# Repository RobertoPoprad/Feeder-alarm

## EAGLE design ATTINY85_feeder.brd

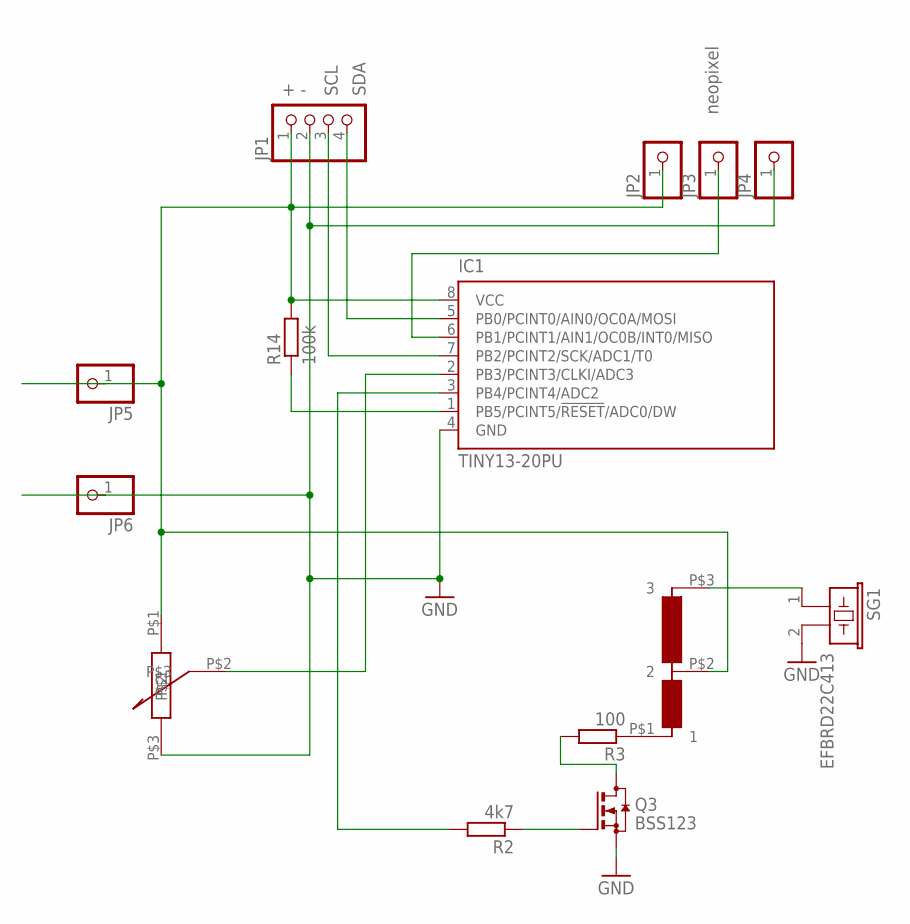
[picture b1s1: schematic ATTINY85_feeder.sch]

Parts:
IC1: TINY13-20PU; DIL08
JP1: PINHD-1X4; 1X04
JP2, JP3, JP4, JP5, JP6: PINHD-1X1; 1X01
Q3: BSS123; SOT23
R2: 4k7; 0204/7
R3: 100; 0204/7
R14: 100k; 0204/7
SG1: EFBRD22C413
U$1: POTENCIOMETER
U$3: AUTOTRAFO

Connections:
GND: IC1.4 (GND), JP1.2, JP4.1, JP6.1, Q3.2 (S), SG1.2, U$1.P$3
unnamed: IC1.3 (PB4/PCINT4/ADC2), R2.2
unnamed: IC1.6 (PB1/PCINT1/AIN1/OC0B/INT0/MISO), JP3.1
unnamed: IC1.7 (PB2/PCINT2/SCK/ADC1/T0), JP1.3
unnamed: IC1.2 (PB3/PCINT3/CLKI/ADC3), U$1.P$2
unnamed: IC1.5 (PB0/PCINT0/AIN0/OC0A/MOSI), JP1.4
unnamed: IC1.1 (PB5/PCINT5/!RESET!/ADC0/DW), R14.1
unnamed: R3.1, U$3.P$1 (1)
unnamed: Q3.1 (G), R2.1
unnamed: SG1.1, U$3.P$3 (3)
unnamed: Q3.3 (D), R3.2
unnamed: IC1.8 (VCC), JP1.1, JP2.1, JP5.1, R14.2, U$1.P$1, U$3.P$2 (2)

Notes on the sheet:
SCL
SDA
neopixel

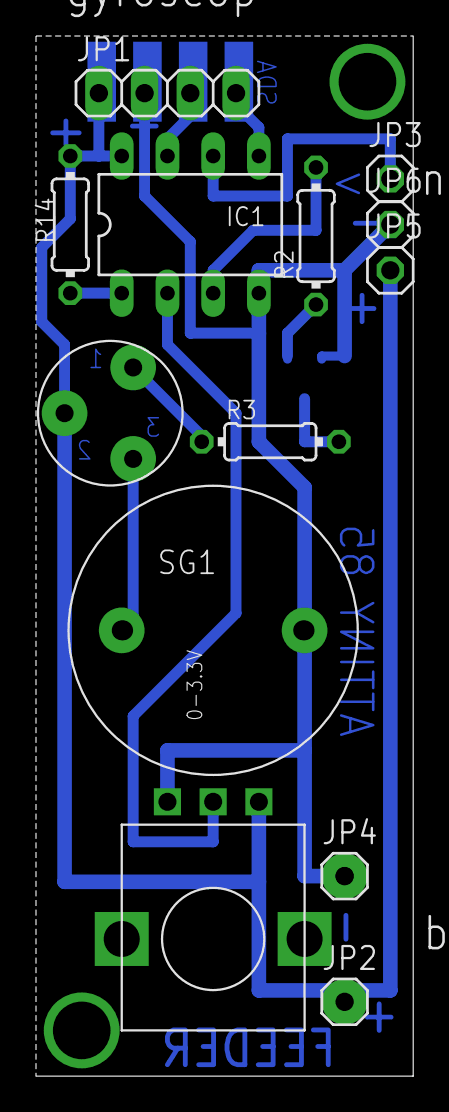
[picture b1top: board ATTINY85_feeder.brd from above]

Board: 2 copper layers, 21.0 x 57.8 mm, 14 parts (1 on the bottom side), 12 nets.
